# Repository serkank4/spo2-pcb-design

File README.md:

# SpO2 (Pulse Oximeter) PCB Design

This repository contains my very first PCB design using KiCad EDA. It was created as a learning project to understand the complete hardware design workflow, from schematic capture to generating production-ready Gerber files.

##  Project Details

- **EDA Tool:** KiCad
- **Board Type:** 2-Layer Printed Circuit Board (PCB)
- **Status:** Designed & Routed (Gerber files generated)

### Key Achievements
1. **Schematic Design:** Successfully mapped out the circuit logic and connections from scratch.
2. **Custom Libraries:** Created custom schematic symbols and PCB footprints (`spo2_stuff`) for components not available in the standard KiCad library.
3. **PCB Routing:** Manually completed component placement and routed all copper traces for a 2-layer board layout.
4. **Manufacturing Export:** Generated standard, ready-to-manufacture Gerber and Drill files.

---

## Visual Showcase

| 3D Render | Schematic | PCB Layout |
|:---:|:---:|:---:|
|  |  |  |

---

## Repository Structure

* `*.kicad_sch` — Schematic source file.
* `*.kicad_pcb` — PCB layout design file.
* `spo2_stuff*/` — Custom symbol and footprint libraries designed specifically for this project.
* `gerbers/` — Fabrication output files ready for actual manufacturing.

---

*If you have any feedback or tips for a beginner hardware designer, feel free to open an issue or reach out!*

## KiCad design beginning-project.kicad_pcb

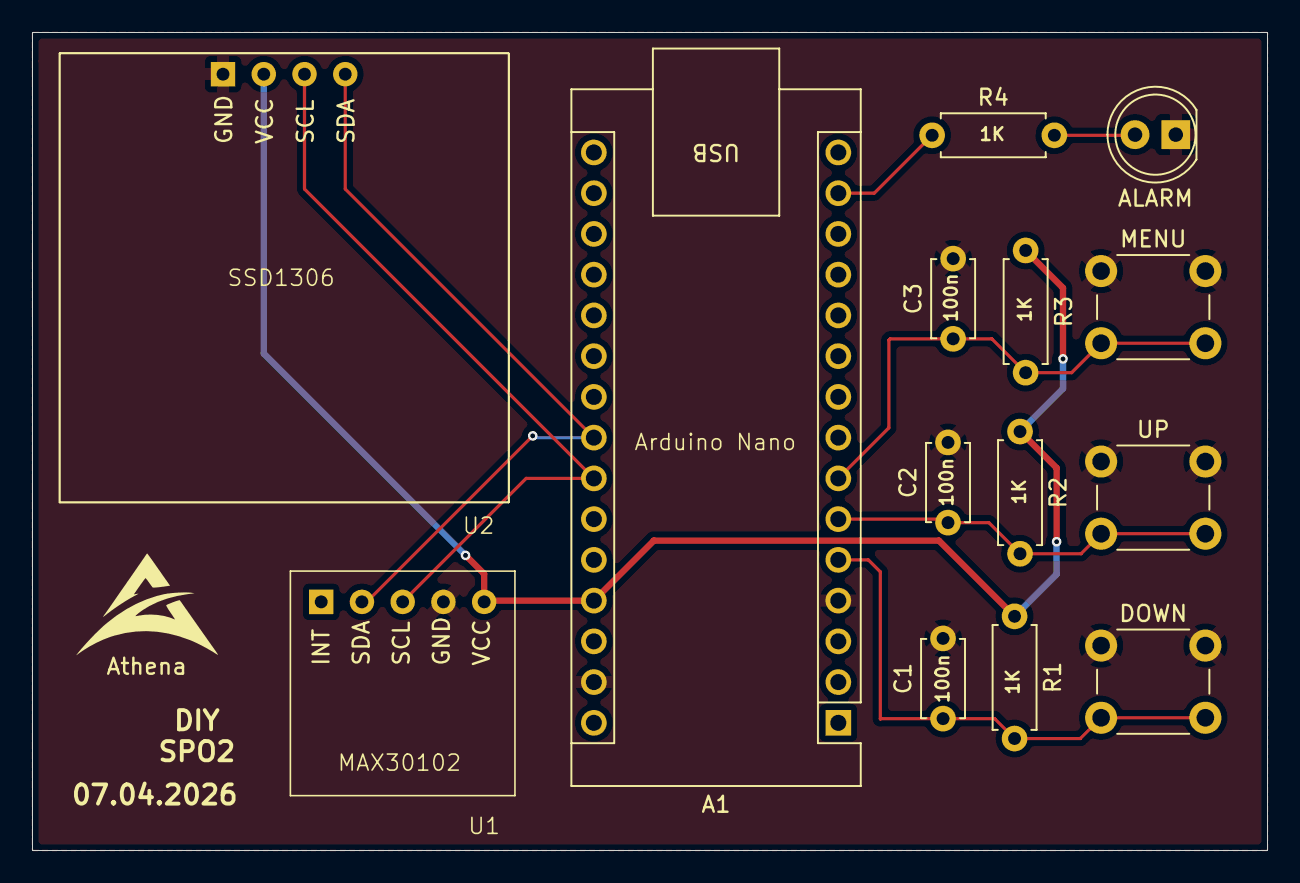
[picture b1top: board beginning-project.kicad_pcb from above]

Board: 2 copper layers, 77.0 x 51.0 mm, 14 parts (0 on the bottom side), 9 nets.

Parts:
A1: Arduino_Nano_v3.x; Arduino_Nano
ALARM: LED; LED_D5.0mm
C1, C2, C3: 100n; C_Disc_D4.7mm_W2.5mm_P5.00mm
DOWN: SW_Push; SW_PUSH_6mm_H5mm
MENU: SW_Push; SW_PUSH_6mm_H5mm
R1, R2, R3, R4: 1k; R_Axial_DIN0207_L6.3mm_D2.5mm_P7.62mm_Horizontal
U1: MAX30102; MAX30102_Module
U2: SSD1306
UP: SW_Push; SW_PUSH_6mm_H5mm

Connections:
+5V: A1.27 (+5V), R1.1, R2.1, R3.1, U1.5 (VCC), U2.2 (VCC)
/SCL: A1.24 (A5), U1.3 (SCL), U2.3 (SCL)
/SDA: A1.23 (A4), U1.2 (SDA), U2.4 (SDA)
GND: A1.4 (GND), A1.29 (GND), ALARM.1 (K), C1.2, C2.2, C3.2, DOWN.1, MENU.1, U1.4 (GND), U2.1 (GND), UP.1
unnamed: A1.5 (D2), C1.1, DOWN.2, R1.2
unnamed: A1.6 (D3), C2.1, R2.2, UP.2
unnamed: A1.7 (D4), C3.1, MENU.2, R3.2
unnamed: A1.14 (D11), R4.1
unnamed: ALARM.2 (A), R4.2

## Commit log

2026-04-09 My first KiCad project: SpO2 PCB design
2026-04-10 chore: remove stock MAX30102 module from schematic
